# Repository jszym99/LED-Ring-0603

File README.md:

# LED Ring 0603

The custom PCB for the [LED Ring](https://github.com/jszym99/LEDRing) project. The board carries a ring of 72 0603 LEDs, driven by an ATtiny84A and powered from a CR2032 coin cell. An ADXL367 accelerometer on the board lets the firmware react to motion.

## Features

- 72 x 0603 LEDs arranged in a ring, Charlieplexed on 9 pins (9 x 8 = 72)
- ATtiny84A microcontroller using its internal oscillator
- ADXL367 3-axis accelerometer connected over I2C, with an interrupt line (`INT0`) to the microcontroller
- Powered by a single cell in a Keystone 3034 1x20 mm battery holder
- 4-layer PCB

## Schematic

The design is hierarchical. The root sheet `LED Ring 0603.kicad_sch` contains four sub-sheets:

| Sheet | File | Contents |
|:---|:---|:---|
| Led Matrix | `ledmatrix.kicad_sch` | The 72 LEDs |
| MCU | `microcontroller.kicad_sch` | ATtiny84A |
| Accelerometer | `accelerometer.kicad_sch` | ADXL367 and the `I2C` and `INT0` signals |
| Power | `power.kicad_sch` | Battery |

A PDF of the schematic is at `PDFs/LED Ring 0603.pdf`.

## PCB

The board layout is in `LED Ring 0603.kicad_pcb`, with a PDF print at `PDFs/LED Ring 0603 PCB.pdf`.

## Notes

- Ensure the 0603 LED footprint polarity matches the part you order before assembly
- The PCB has no dedicated programming connector. Program the microcontroller by attaching a SOIC-14 clip directly to it
- The board is designed for JLCPCB fabrication and assembly, and the design rules in the KiCad project are set to its manufacturing capabilities
- Production files for JLCPCB, generated with the Fabrication Toolkit plugin, are in `production/`. `LED_Ring_0603.zip` is for fabrication, and `bom.csv` and `positions.csv` are for assembly

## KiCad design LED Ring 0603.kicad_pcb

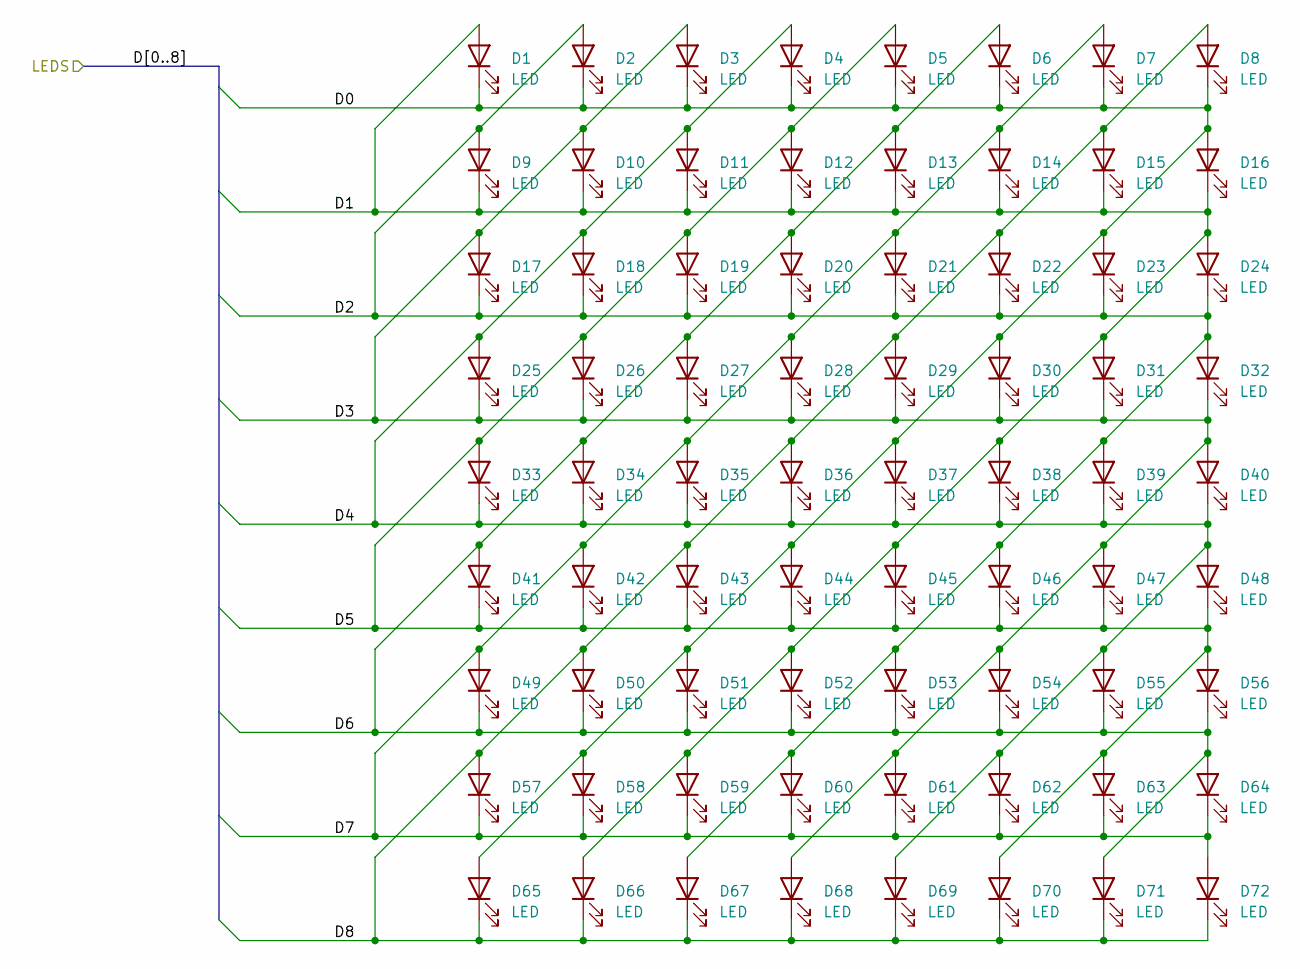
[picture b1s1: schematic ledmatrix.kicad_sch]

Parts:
D1, D2, D3, D4, D5, D6, D7, D8, D9, D10, D11, D12, D13, D14, D15, D16, D17, D18, D19, D20, D21, D22, D23, D24, D25, D26, D27, D28, D29, D30, D31, D32, D33, D34, D35, D36, D37, D38, D39, D40, D41, D42, D43, D44, D45, D46, D47, D48, D49, D50, D51, D52, D53, D54, D55, D56, D57, D58, D59, D60, D61, D62, D63, D64, D65, D66, D67, D68, D69, D70, D71, D72: LED; LED_0603_1608Metric

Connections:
/Led Matrix/D0: D1.1 (K), D2.1 (K), D3.1 (K), D4.1 (K), D5.1 (K), D6.1 (K), D7.1 (K), D8.1 (K), D16.2 (A), D23.2 (A), D30.2 (A), D37.2 (A), D44.2 (A), D51.2 (A), D58.2 (A), D65.2 (A); also elsewhere on the board
/Led Matrix/D1: D1.2 (A), D9.1 (K), D10.1 (K), D11.1 (K), D12.1 (K), D13.1 (K), D14.1 (K), D15.1 (K), D16.1 (K), D24.2 (A), D31.2 (A), D38.2 (A), D45.2 (A), D52.2 (A), D59.2 (A), D66.2 (A); also elsewhere on the board
/Led Matrix/D2: D2.2 (A), D9.2 (A), D17.1 (K), D18.1 (K), D19.1 (K), D20.1 (K), D21.1 (K), D22.1 (K), D23.1 (K), D24.1 (K), D32.2 (A), D39.2 (A), D46.2 (A), D53.2 (A), D60.2 (A), D67.2 (A); also elsewhere on the board
/Led Matrix/D3: D3.2 (A), D10.2 (A), D17.2 (A), D25.1 (K), D26.1 (K), D27.1 (K), D28.1 (K), D29.1 (K), D30.1 (K), D31.1 (K), D32.1 (K), D40.2 (A), D47.2 (A), D54.2 (A), D61.2 (A), D68.2 (A); also elsewhere on the board
/Led Matrix/D4: D4.2 (A), D11.2 (A), D18.2 (A), D25.2 (A), D33.1 (K), D34.1 (K), D35.1 (K), D36.1 (K), D37.1 (K), D38.1 (K), D39.1 (K), D40.1 (K), D48.2 (A), D55.2 (A), D62.2 (A), D69.2 (A); also elsewhere on the board
/Led Matrix/D5: D5.2 (A), D12.2 (A), D19.2 (A), D26.2 (A), D33.2 (A), D41.1 (K), D42.1 (K), D43.1 (K), D44.1 (K), D45.1 (K), D46.1 (K), D47.1 (K), D48.1 (K), D56.2 (A), D63.2 (A), D70.2 (A); also elsewhere on the board
/Led Matrix/D6: D6.2 (A), D13.2 (A), D20.2 (A), D27.2 (A), D34.2 (A), D41.2 (A), D49.1 (K), D50.1 (K), D51.1 (K), D52.1 (K), D53.1 (K), D54.1 (K), D55.1 (K), D56.1 (K), D64.2 (A), D71.2 (A); also elsewhere on the board
/Led Matrix/D7: D7.2 (A), D14.2 (A), D21.2 (A), D28.2 (A), D35.2 (A), D42.2 (A), D49.2 (A), D57.1 (K), D58.1 (K), D59.1 (K), D60.1 (K), D61.1 (K), D62.1 (K), D63.1 (K), D64.1 (K), D72.2 (A); also elsewhere on the board
/Led Matrix/D8: D8.2 (A), D15.2 (A), D22.2 (A), D29.2 (A), D36.2 (A), D43.2 (A), D50.2 (A), D57.2 (A), D65.1 (K), D66.1 (K), D67.1 (K), D68.1 (K), D69.1 (K), D70.1 (K), D71.1 (K), D72.1 (K); also elsewhere on the board

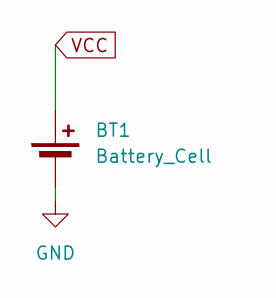
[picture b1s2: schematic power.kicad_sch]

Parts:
BT1: Battery_Cell; BatteryHolder_Keystone_3034_1x20mm

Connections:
GND: BT1.2 (-); also elsewhere on the board
VCC: BT1.1 (+); also elsewhere on the board

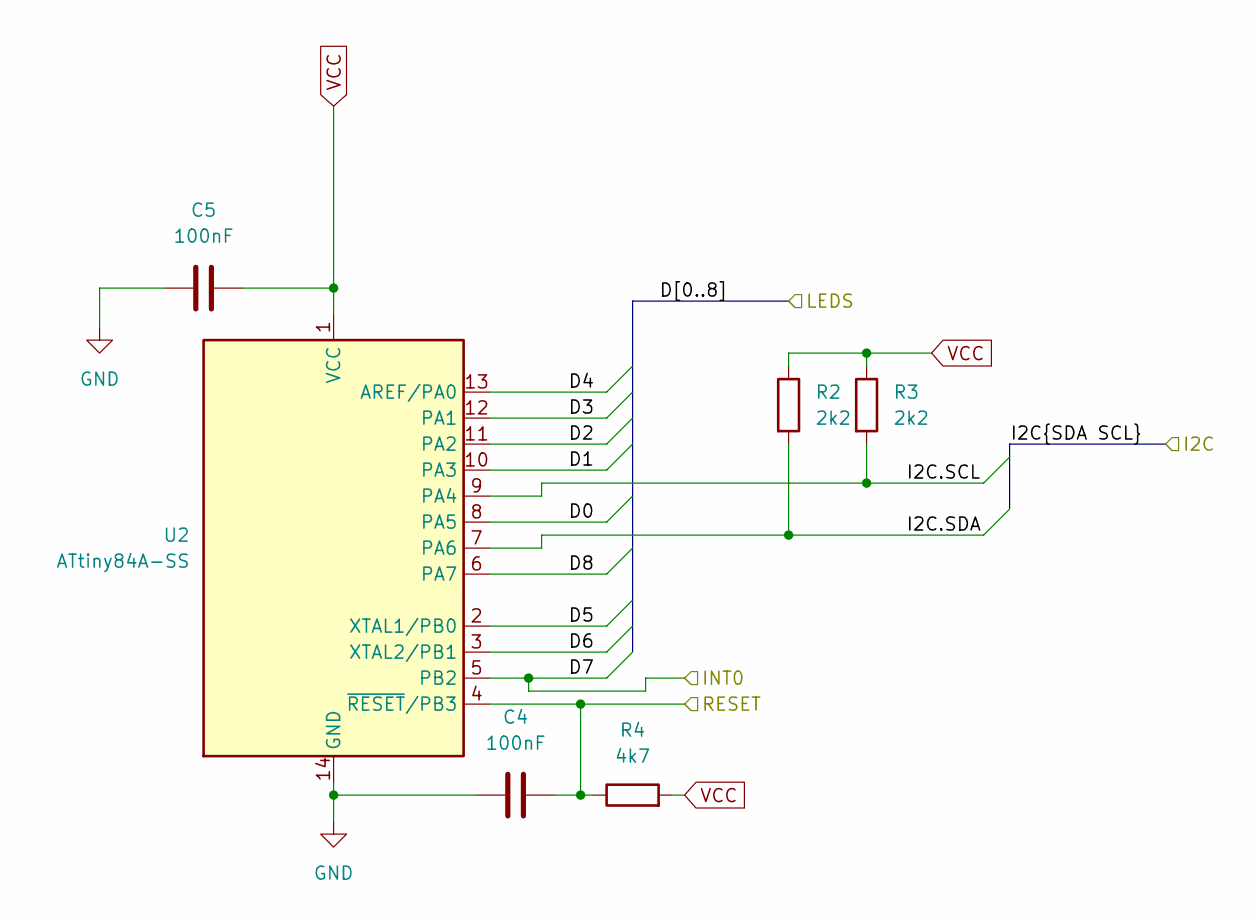
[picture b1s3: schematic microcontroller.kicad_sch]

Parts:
C4, C5: 100nF; C_0603_1608Metric
R2, R3: 2k2; R_0603_1608Metric
R4: 4k7; R_0603_1608Metric
U2: ATtiny84A-SS; SOIC-14_3.9x8.7mm_P1.27mm

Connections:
/Accelerometer/I2C.SCL: R3.2, U2.9 (PA4); also elsewhere on the board
/Accelerometer/I2C.SDA: R2.2, U2.7 (PA6); also elsewhere on the board
/Accelerometer/RESET: C4.1, R4.1, U2.4 (~RESET/PB3); also elsewhere on the board
/Led Matrix/D0: U2.8 (PA5); also elsewhere on the board
/Led Matrix/D1: U2.10 (PA3); also elsewhere on the board
/Led Matrix/D2: U2.11 (PA2); also elsewhere on the board
/Led Matrix/D3: U2.12 (PA1); also elsewhere on the board
/Led Matrix/D4: U2.13 (AREF/PA0); also elsewhere on the board
/Led Matrix/D5: U2.2 (XTAL1/PB0); also elsewhere on the board
/Led Matrix/D6: U2.3 (XTAL2/PB1); also elsewhere on the board
/Led Matrix/D7: U2.5 (PB2); also elsewhere on the board
/Led Matrix/D8: U2.6 (PA7); also elsewhere on the board
GND: C4.2, C5.1, U2.14 (GND); also elsewhere on the board
VCC: C5.2, R2.1, R3.1, R4.2, U2.1 (VCC); also elsewhere on the board

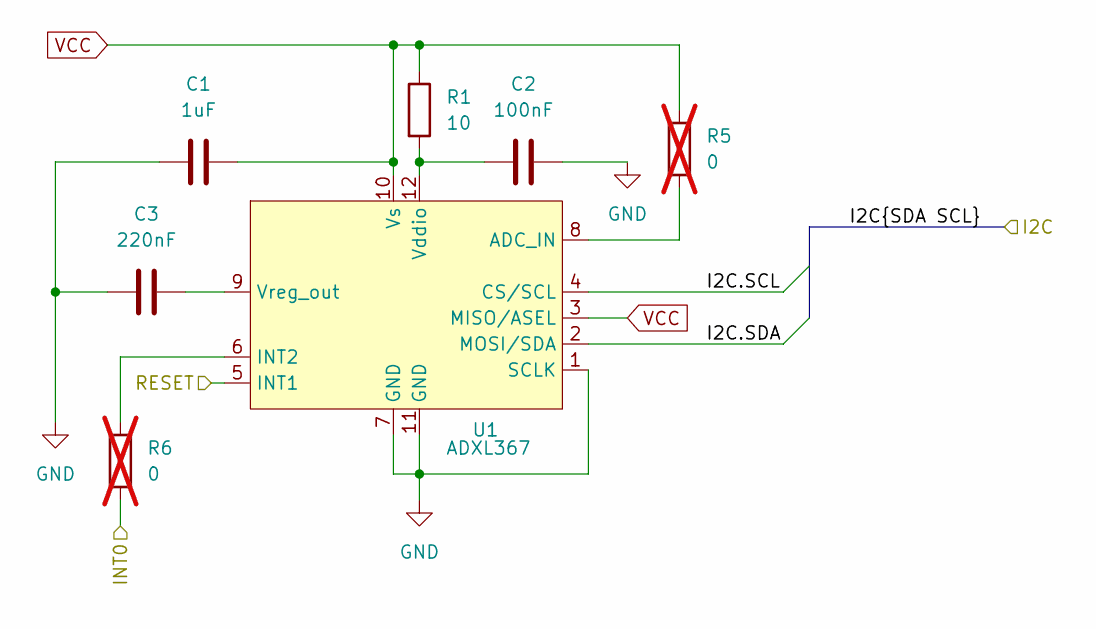
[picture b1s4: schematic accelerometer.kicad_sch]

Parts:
C1: 1uF; C_0603_1608Metric
C2: 100nF; C_0603_1608Metric
C3: 220nF; C_0603_1608Metric
R1: 10; R_0603_1608Metric
R5, R6: 0; R_0603_1608Metric; not fitted
U1: ADXL367; LGA-12_2x2mm_P0.5mm

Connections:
/Accelerometer/I2C.SCL: U1.4 (CS/SCL); also elsewhere on the board
/Accelerometer/I2C.SDA: U1.2 (MOSI/SDA); also elsewhere on the board
/Accelerometer/RESET: U1.5 (INT1); also elsewhere on the board
/Led Matrix/D7: R6.2; also elsewhere on the board
GND: C1.1, C2.1, C3.1, U1.1 (SCLK), U1.7 (GND), U1.11 (GND); also elsewhere on the board
unnamed: R5.2, U1.8 (ADC_IN)
unnamed: R6.1, U1.6 (INT2)
unnamed: C2.2, R1.2, U1.12 (Vddio)
unnamed: C3.2, U1.9 (Vreg_out)
VCC: C1.2, R1.1, R5.1, U1.3 (MISO/ASEL), U1.10 (Vs); also elsewhere on the board

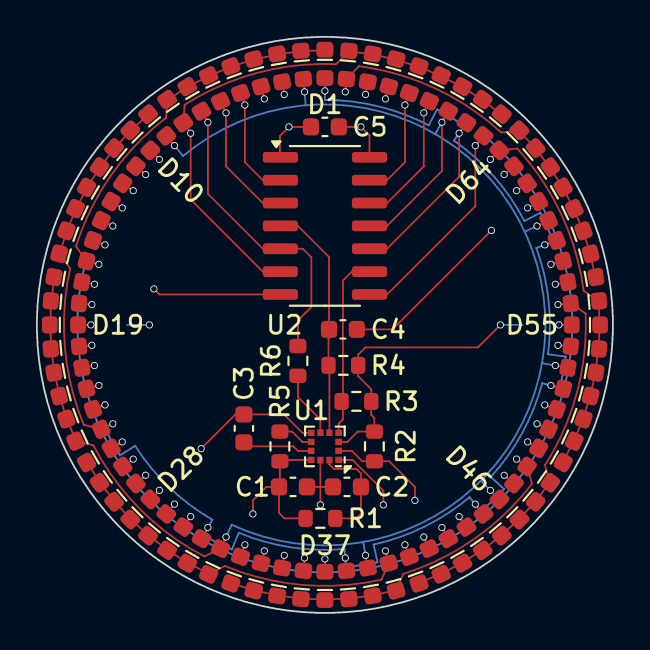
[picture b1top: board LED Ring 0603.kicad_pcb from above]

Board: 4 copper layers, 32.0 x 32.0 mm, 86 parts (1 on the bottom side), 18 nets.

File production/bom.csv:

Designator,Footprint,Quantity,Value,LCSC Part #
BT1,BatteryHolder_Keystone_3034_1x20mm,1,Battery_Cell,
C1,0603,1,1uF,
"C2, C4, C5",0603,3,100nF,
C3,0603,1,220nF,
"D1, D10, D11, D12, D13, D14, D15, D16, D17, D18, D19, D2, D20, D21, D22, D23, D24, D25, D26, D27, D28, D29, D3, D30, D31, D32, D33, D34, D35, D36, D37, D38, D39, D4, D40, D41, D42, D43, D44, D45, D46, D47, D48, D49, D5, D50, D51, D52, D53, D54, D55, D56, D57, D58, D59, D6, D60, D61, D62, D63, D64, D65, D66, D67, D68, D69, D7, D70, D71, D72, D8, D9",0603,72,LED,
R1,0603,1,10,
"R2, R3",0603,2,2k2,
R4,0603,1,4k7,
U1,LGA-12_2x2mm_P0.5mm,1,ADXL367,
U2,SOIC-14_3.9x8.7mm_P1.27mm,1,ATtiny84A-SS,
